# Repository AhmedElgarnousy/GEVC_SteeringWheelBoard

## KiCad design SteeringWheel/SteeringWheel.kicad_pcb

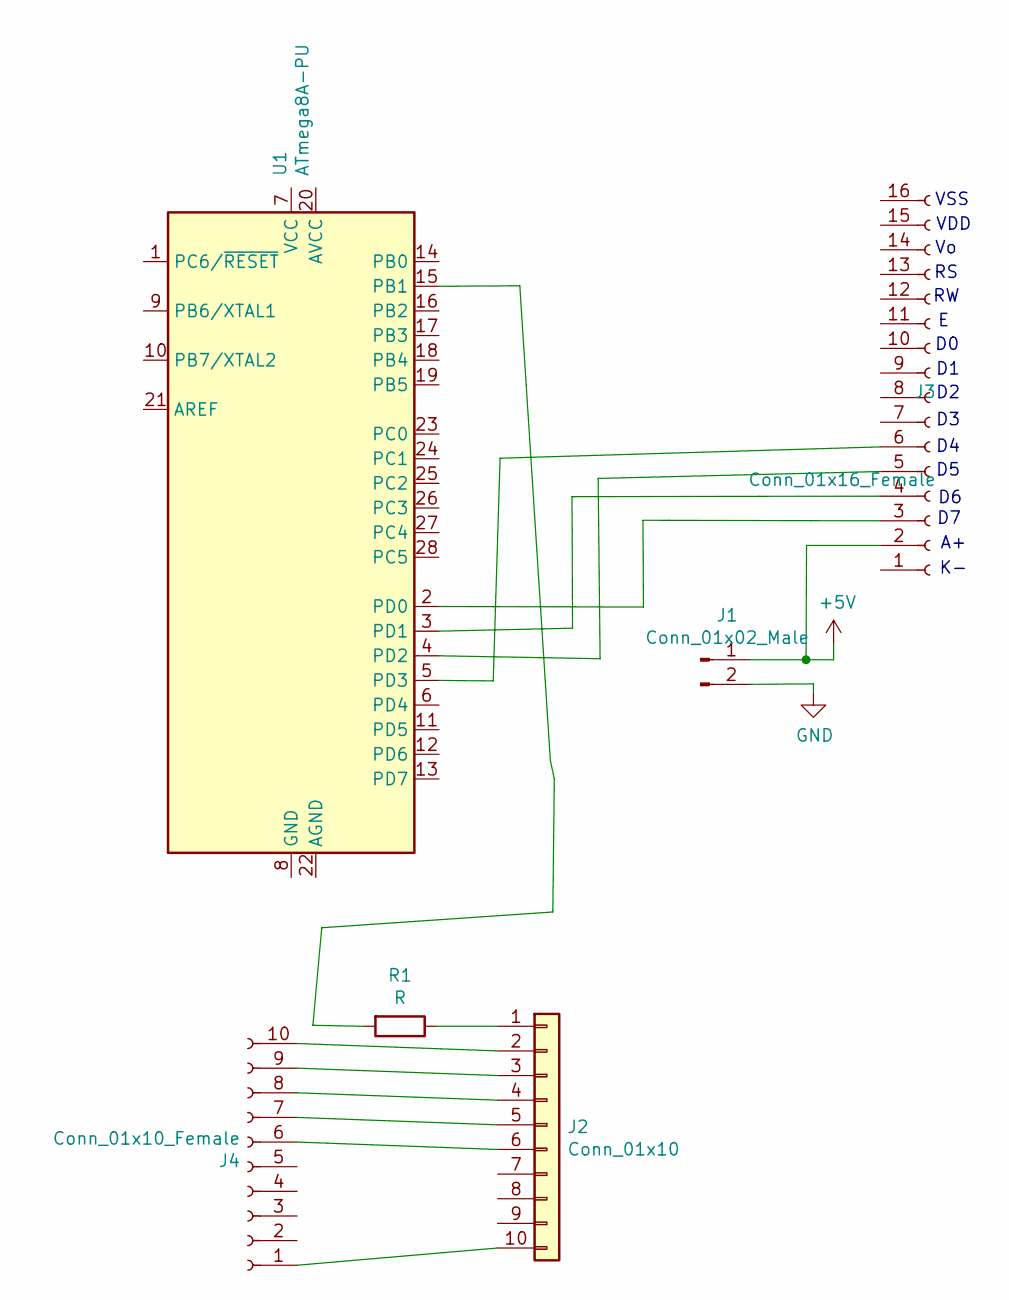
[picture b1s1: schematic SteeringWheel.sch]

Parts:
J1: Conn_01x02_Male; TerminalBlock_Phoenix_MKDS-1,5-2-5.08_1x02_P5.08mm_Horizont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
J2: Conn_01x10; TerminalBlock_Phoenix_MPT-0,5-10-2.54_1x10_P2.54mm_Horizont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
J3: Conn_01x16_Female; PinSocket_1x16_P2.54mm_Vertical
J4: Conn_01x10_Female; TerminalBlock_Phoenix_MPT-0,5-10-2.54_1x10_P2.54mm_Horizont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
R1: R; R_Axial_DIN0204_L3.6mm_D1.6mm_P7.62mm_Horizontal
U1: ATmega8A-PU; DIP-28_W7.62mm

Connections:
+5V: J1.1, J3.2
GND: J1.2
unnamed: J2.1, R1.1
unnamed: J2.2, J4.10
unnamed: J2.3, J4.9
unnamed: J2.4, J4.8
unnamed: J2.6, J4.6
unnamed: J2.10, J4.1
unnamed: J3.3, U1.2 (PD0)
unnamed: J3.4, U1.3 (PD1)
unnamed: J3.5, U1.4 (PD2)
unnamed: J3.6, U1.5 (PD3)
unnamed: R1.2, U1.15 (PB1)

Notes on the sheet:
VDD
VSS

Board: 2 copper layers, 6 parts (0 on the bottom side), 12 nets, no tracks yet.

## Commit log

2022-08-30 init commit
2022-09-04 Layout
2022-09-13 change 1
2022-09-13 change 2
